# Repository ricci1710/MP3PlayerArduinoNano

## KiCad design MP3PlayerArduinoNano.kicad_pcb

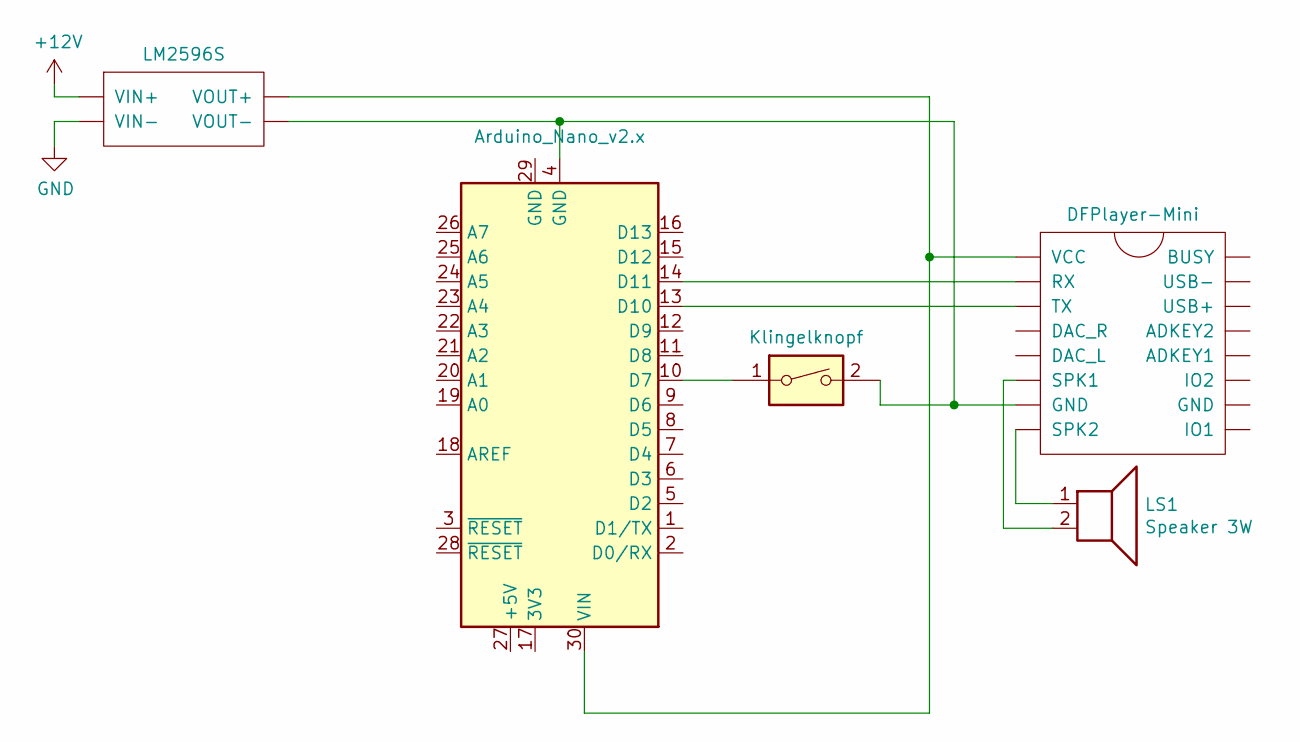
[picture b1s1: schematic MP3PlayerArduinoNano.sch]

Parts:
A1: Arduino_Nano_v2.x; Arduino_Nano
LS1: Speaker 3W; FanPinHeader_1x03_P2.54mm_Vertical
SW1: Klingelknopf; SW_DIP_SPSTx01_Slide_6.7x4.1mm_W7.62mm_P2.54mm_LowProfile
U1: LM2596S
U2: DFPlayer-Mini

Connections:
+12V: U1.1 (VIN+)
GND: U1.2 (VIN-)
unnamed: A1.4 (GND), SW1.2, U1.4 (VOUT-), U2.7 (GND)
unnamed: A1.10 (D7), SW1.1
unnamed: A1.13 (D10), U2.3 (TX)
unnamed: A1.14 (D11), U2.2 (RX)
unnamed: A1.30 (VIN), U1.3 (VOUT+), U2.1 (VCC)
unnamed: LS1.1, U2.8 (SPK2)
unnamed: LS1.2, U2.6 (SPK1)

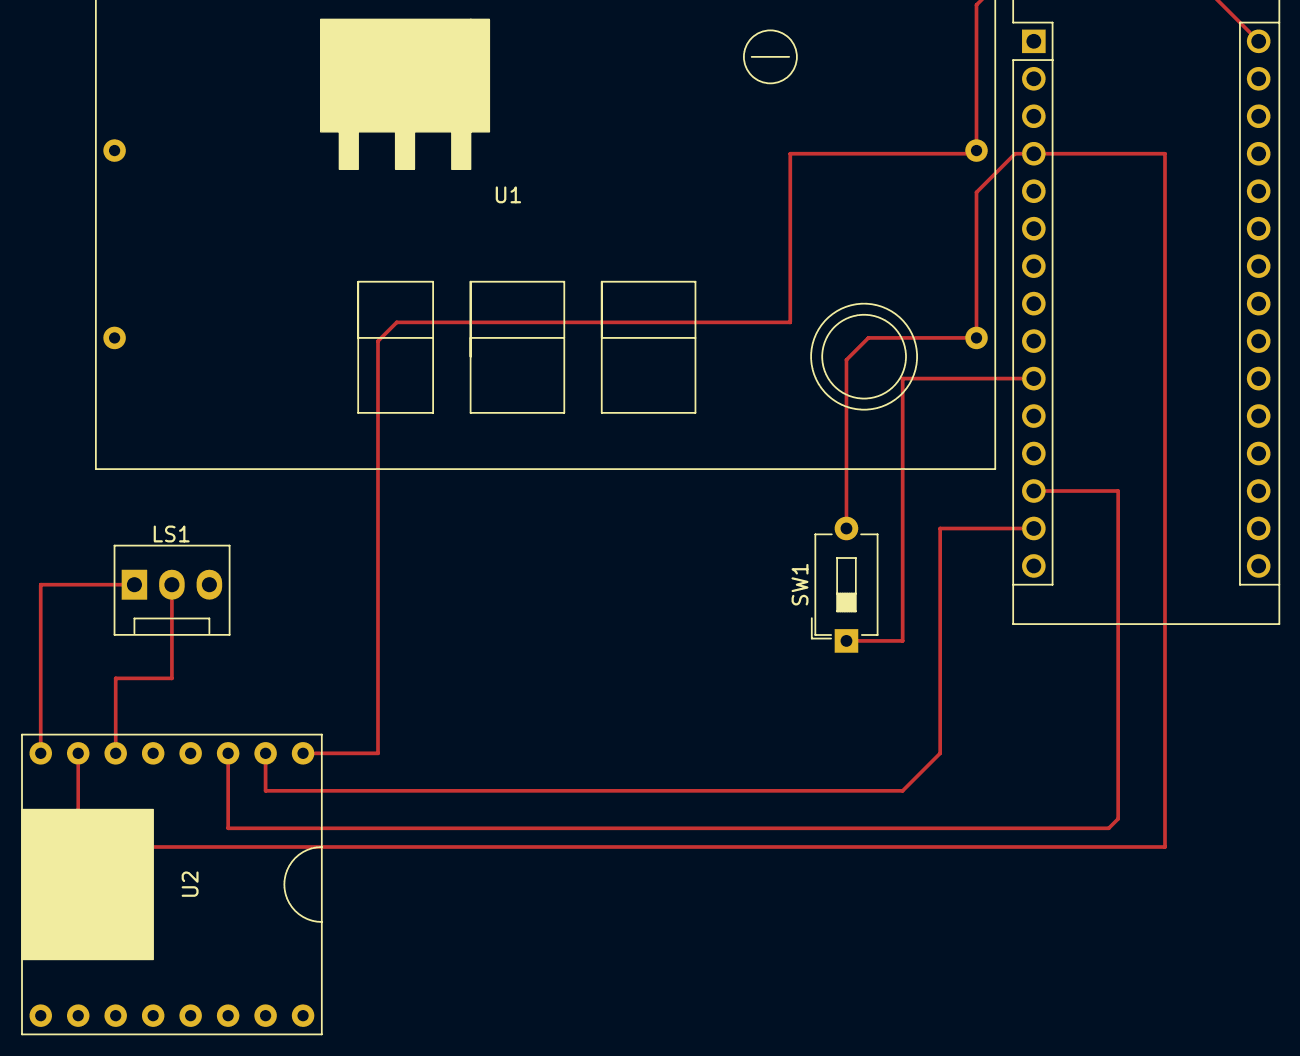
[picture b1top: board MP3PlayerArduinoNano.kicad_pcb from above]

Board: 2 copper layers, 5 parts (0 on the bottom side), 7 nets.

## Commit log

2021-03-22 init
